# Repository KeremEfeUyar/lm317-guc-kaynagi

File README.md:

# lm317-guc-kaynagi

It is used for voltage reduction and stabilization.
It precisely reduces a high and unstable input voltage and/or ensures it remains stable.

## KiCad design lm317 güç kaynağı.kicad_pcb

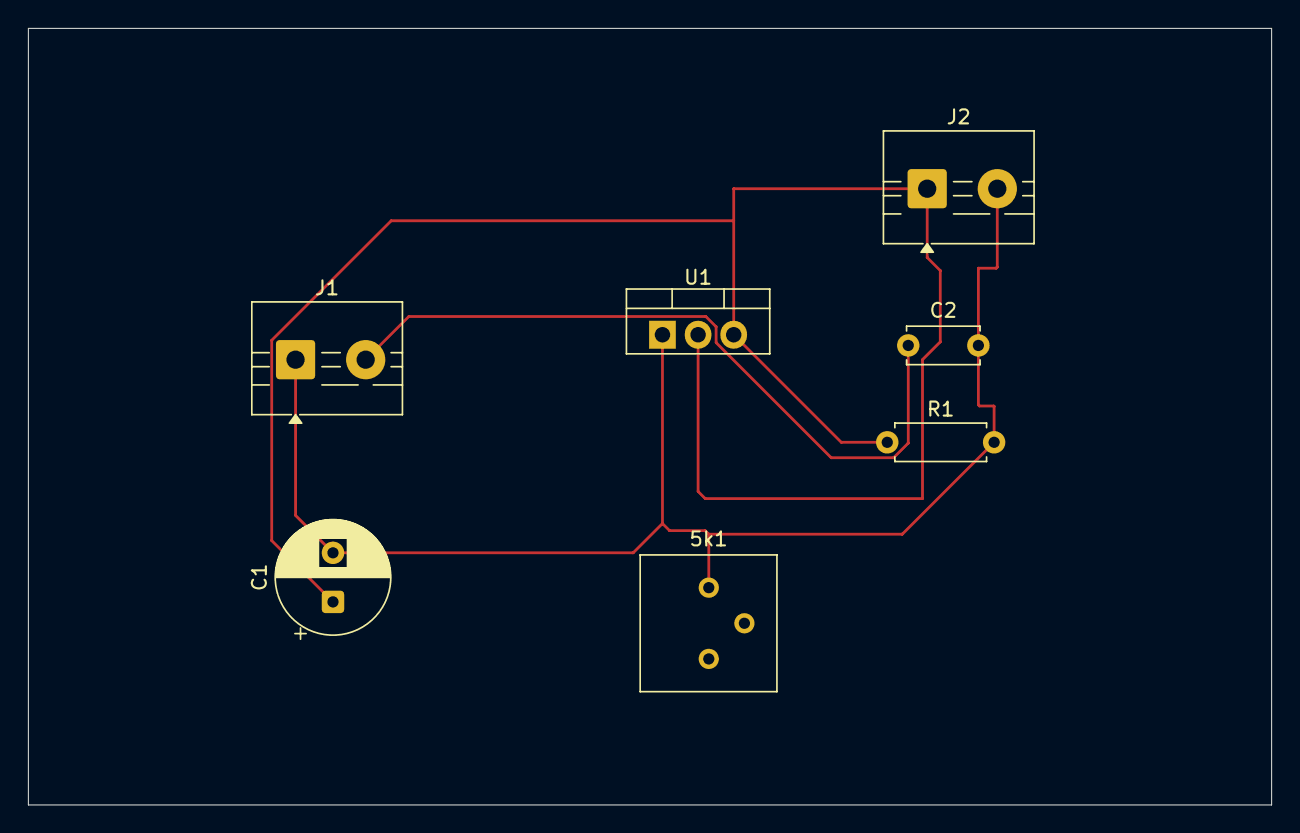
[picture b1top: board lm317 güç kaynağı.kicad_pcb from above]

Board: 2 copper layers, 88.6 x 55.4 mm, 7 parts (0 on the bottom side), 3 nets.

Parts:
5k1: Potentiometer; Potentiometer_Bourns_3386P_Vertical
C1: C_Polarized; CP_Radial_D8.0mm_P3.50mm
C2: C; C_Disc_D5.0mm_W2.5mm_P5.00mm
J1, J2: Conn_01x02_Pin; TerminalBlock_MaiXu_MX126-5.0-02P_1x02_P5.00mm
R1: 240; R_Axial_DIN0207_L6.3mm_D2.5mm_P7.62mm_Horizontal
U1: Lineer Regülatör; TO-220-3_Vertical

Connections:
GND: 5k1.3, C1.2, C2.2, J1.1, J2.2, R1.2, U1.1 (VI)
unnamed: C2.1, J1.2
unnamed: C1.1, J2.1, R1.1, U1.2 (VO), U1.3 (VO)
